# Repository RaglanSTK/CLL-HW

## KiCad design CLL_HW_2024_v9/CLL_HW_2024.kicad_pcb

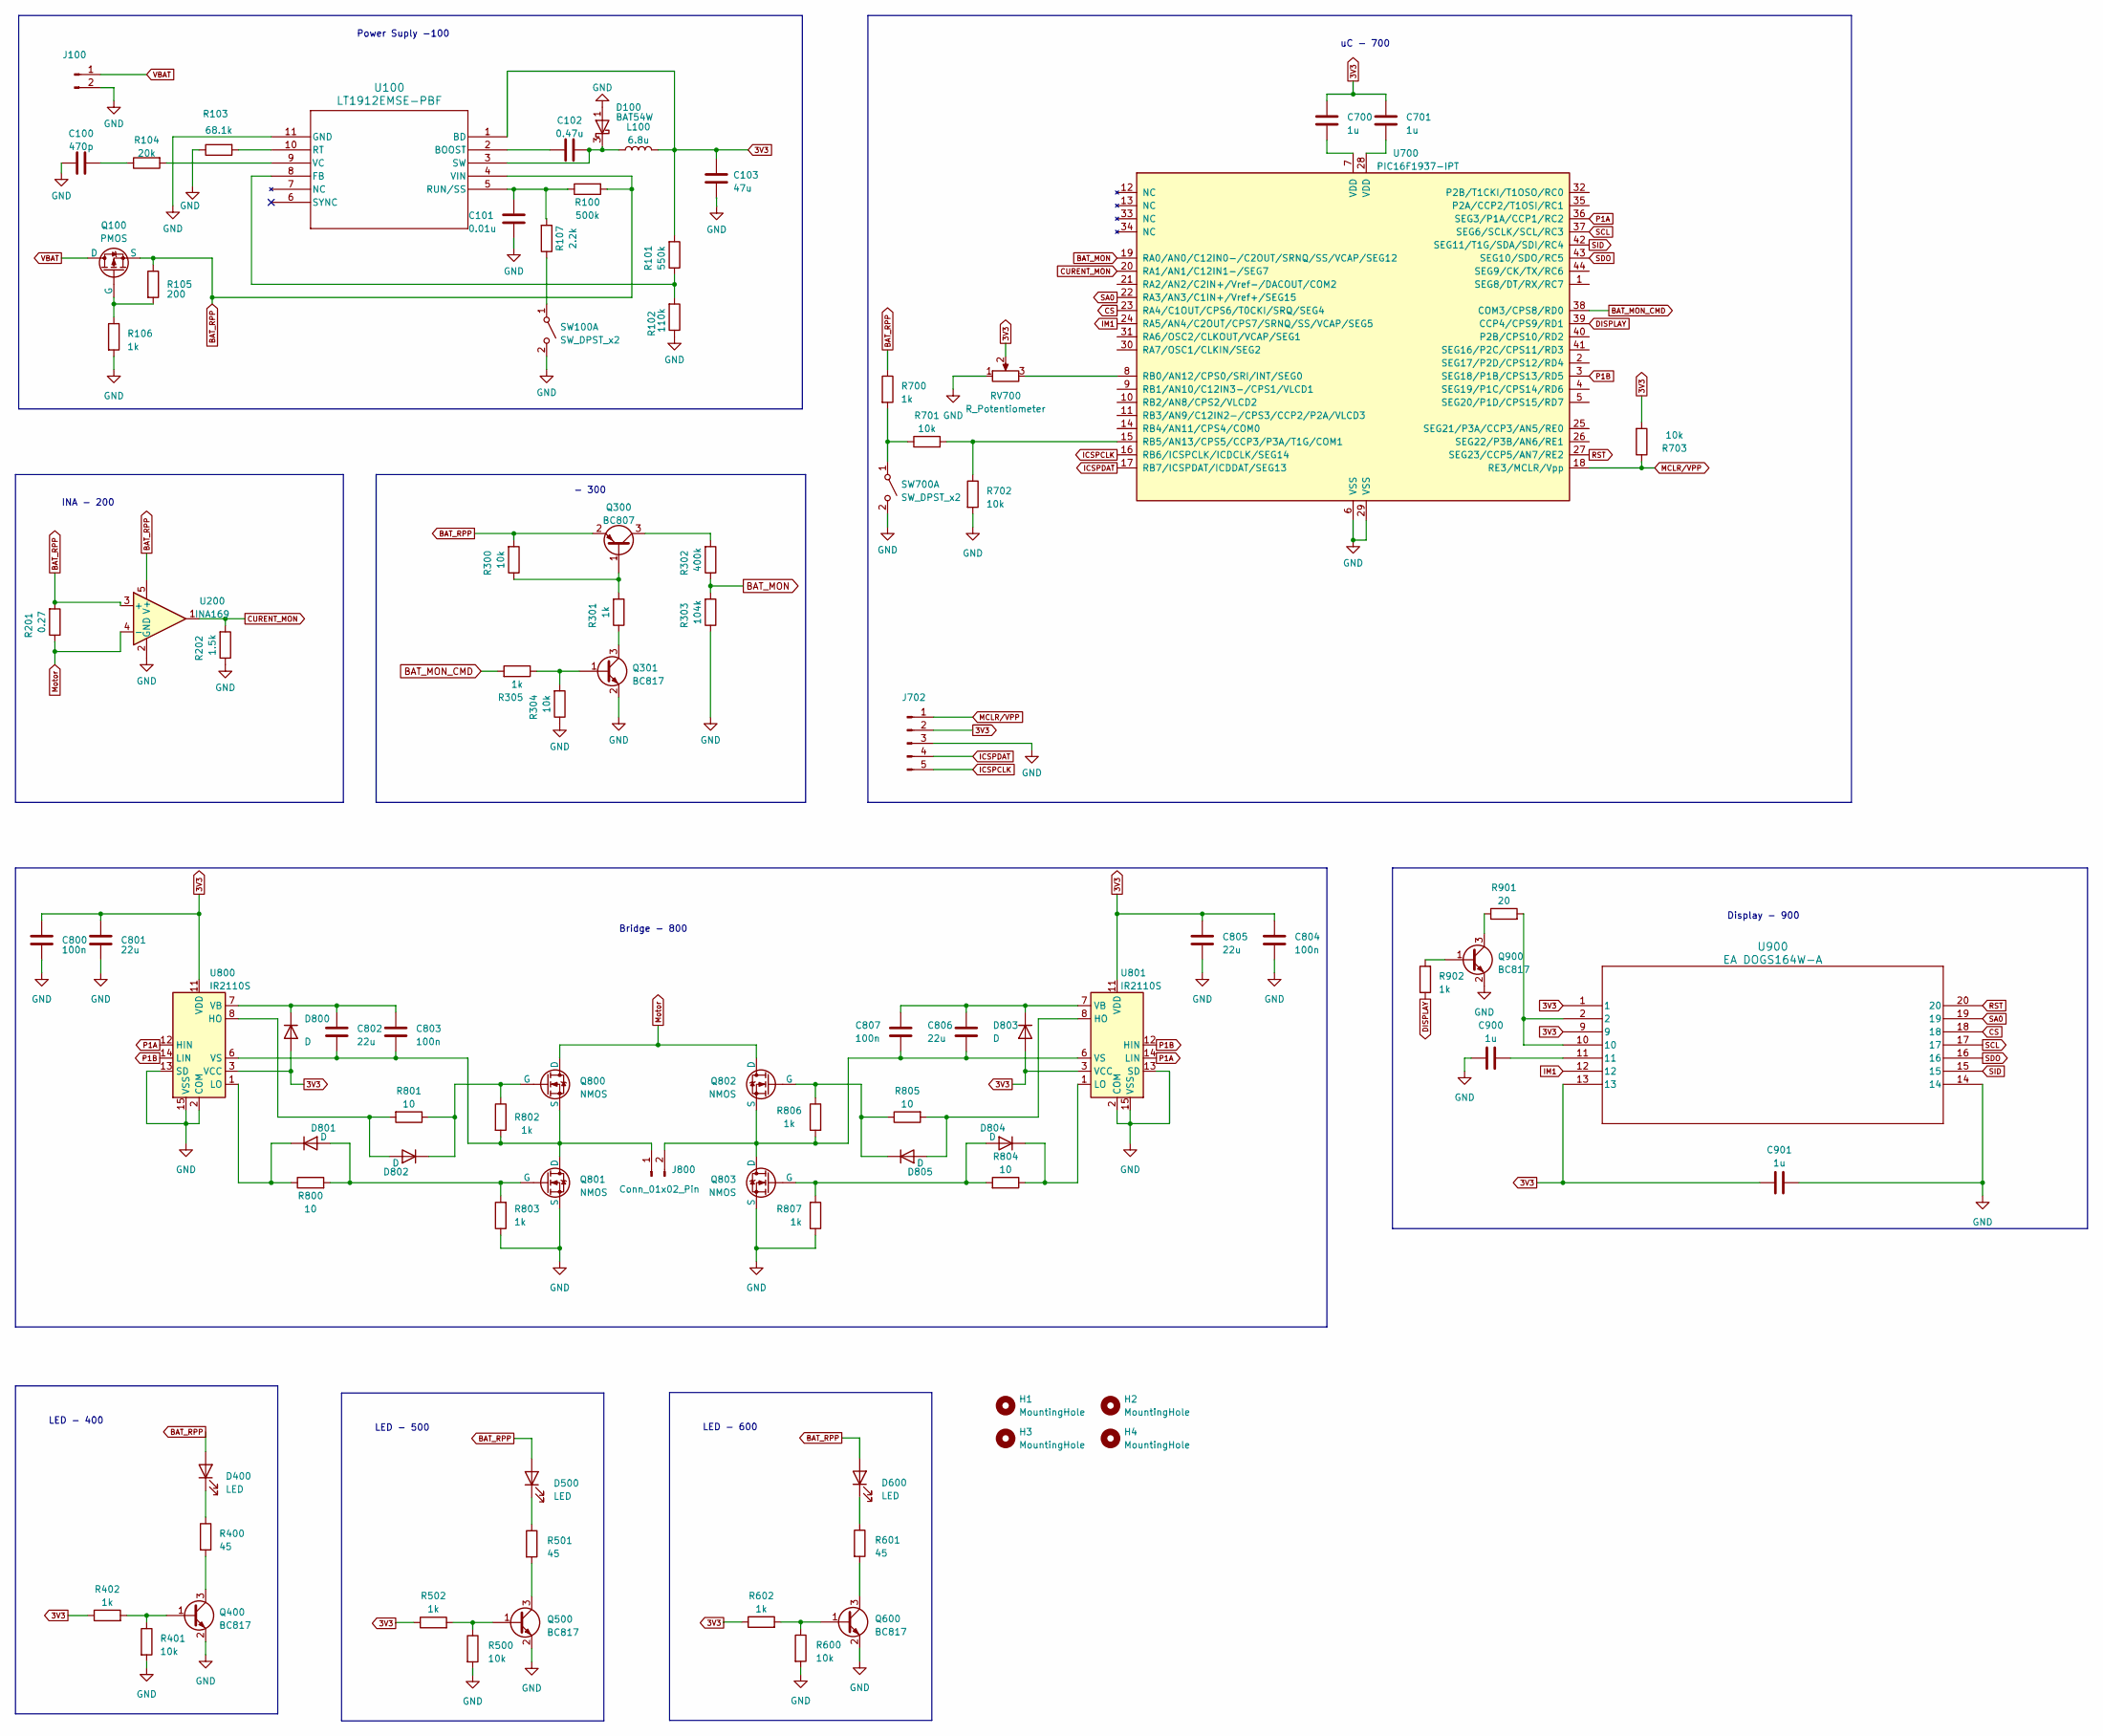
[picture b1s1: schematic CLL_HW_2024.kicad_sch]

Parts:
C100: 470p; C_0805_2012Metric
C101: 0.01u; C_0805_2012Metric
C102: 0.47u; C_0805_2012Metric
C103: 47u; C_0805_2012Metric
C700, C701, C900, C901: 1u; C_0805_2012Metric
C800, C803, C804, C807: 100n; C_0805_2012Metric
C801, C802, C805, C806: 22u; C_0805_2012Metric
D100: BAT54W; SOT-323_SC-70
D400, D500, D600: LED; LED_0805_2012Metric
D800, D801, D802, D803, D804, D805: D; D_SOD-323
H1, H2, H3, H4: MountingHole; MountingHole_2.5mm
J100, J800: Conn_01x02_Pin; TerminalBlock_bornier-2_P5.08mm
J702: Conn_01x05_Pin; PinHeader_1x05_P2.54mm_Vertical
L100: 6.8u; L_0805_2012Metric
Q100: PMOS; SOT-23
Q300: BC807; SOT-323_SC-70
Q301, Q400, Q500, Q600, Q900: BC817; SOT-323_SC-70
Q800, Q801, Q802, Q803: NMOS; SOT-23
R100: 500k; R_0805_2012Metric
R101: 550k; R_0805_2012Metric
R102: 110k; R_0805_2012Metric
R103: 68.1k; R_0805_2012Metric
R104: 20k; R_0805_2012Metric
R105: 200; R_0805_2012Metric
R106, R301, R305, R402, R502, R602, R700, R802, R803, R806, R807, R902: 1k; R_0805_2012Metric
R107: 2.2k; R_0805_2012Metric
R201: 0.27; R_0805_2012Metric
R202: 1.5k; R_0805_2012Metric
R300, R304, R401, R500, R600, R701, R702, R703: 10k; R_0805_2012Metric
R302: 400k; R_0805_2012Metric
R303: 104k; R_0805_2012Metric
R400, R501, R601: 45; R_0805_2012Metric
R800, R801, R804, R805: 10; R_0805_2012Metric
R901: 20; R_0805_2012Metric
RV700: R_Potentiometer; Potentiometer_ACP_CA6-H2,5_Horizontal
SW100, SW700: SW_DPST_x2; SW2_GF-123-0054_CWI
U100: LT1912EMSE-PBF; MSOP-10-1EP_3x3mm_P0.5mm_EP1.68x1.88mm_ThermalVias
U200: INA169; SOT-23-5
U700: PIC16F1937-IPT; TQFP-44_10x10mm_P0.8mm
U800, U801: IR2110S; SOIC-16W_7.5x10.3mm_P1.27mm
U900: EA DOGS164W-A; EA_DOGS104X-A

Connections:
3V3: C103.1, C700.1, C701.1, C800.1, C801.1, C804.1, C805.1, C901.1, D800.2 (A), D803.2 (A), J702.2, L100.2, R101.2, R402.1, R502.1, R602.1, R703.2, RV700.2, U100.1 (BD), U800.3 (VCC), U800.11 (VDD), U801.3 (VCC), U801.11 (VDD), U900.1, U900.9, U900.13
BAT_MON: R302.1, R303.2, U700.19 (RA0/AN0/C12IN0-/C2OUT/SRNQ/SS/VCAP/SEG12)
BAT_MON_CMD: R305.2, U700.38 (COM3/CPS8/RD0)
BAT_RPP: D400.2 (A), D500.2 (A), D600.2 (A), Q100.3 (S), Q300.2 (E), R100.2, R105.1, R201.2, R300.2, R700.1, U100.4 (VIN), U200.3 (+), U200.5 (V+)
CS: U700.23 (RA4/C1OUT/CPS6/T0CKI/SRQ/SEG4), U900.18
CURENT_MON: R202.2, U200.1, U700.20 (RA1/AN1/C12IN1-/SEG7)
DISPLAY: R902.1, U700.39 (CCP4/CPS9/RD1)
GND: C100.2, C101.2, C103.2, C800.2, C801.2, C804.2, C805.2, C900.1, C901.2, D100.1 (A), J100.2, J702.3, Q301.2 (E), Q400.2 (E), Q500.2 (E), Q600.2 (E), Q801.3 (S), Q803.3 (S), Q900.2 (E), R102.1, R103.1, R106.2, R202.1, R303.1, R304.1, R401.2, R500.2, R600.2, R702.2, R803.1, R807.1, RV700.1, SW100.2 (B), SW700.2 (B), U100.11 (GND), U200.2 (GND), U700.6 (VSS), U700.29 (VSS), U800.2 (COM), U800.13 (SD), U800.15 (VSS), U801.2 (COM), U801.13 (SD), U801.15 (VSS), U900.14
ICSPCLK: J702.5, U700.16 (RB6/ICSPCLK/ICDCLK/SEG14)
ICSPDAT: J702.4, U700.17 (RB7/ICSPDAT/ICDDAT/SEG13)
IM1: U700.24 (RA5/AN4/C2OUT/CPS7/SRNQ/SS/VCAP/SEG5), U900.12
MCLR/VPP: J702.1, R703.1, U700.18 (RE3/MCLR/Vpp)
Motor: Q800.1 (D), Q802.1 (D), R201.1, U200.4 (-)
unnamed: C100.1, R104.1
unnamed: C700.2, U700.7 (VDD)
unnamed: C701.2, U700.28 (VDD)
unnamed: C900.2, U900.11
unnamed: C102.1, D100.3 (K), L100.1, U100.3 (SW)
unnamed: D400.1 (K), R400.1
unnamed: D500.1 (K), R501.1
unnamed: D600.1 (K), R601.1
unnamed: C802.1, C803.1, D800.1 (K), U800.7 (VB)
unnamed: D801.2 (A), Q801.2 (G), R800.2, R803.2
unnamed: D801.1 (K), R800.1, U800.1 (LO)
unnamed: D802.2 (A), R801.2, U800.8 (HO)
unnamed: D802.1 (K), Q800.2 (G), R801.1, R802.1
unnamed: C806.1, C807.1, D803.1 (K), U801.7 (VB)
unnamed: D804.2 (A), Q803.2 (G), R804.2, R807.2
unnamed: D804.1 (K), R804.1, U801.1 (LO)
unnamed: D805.2 (A), R805.2, U801.8 (HO)
unnamed: D805.1 (K), Q802.2 (G), R805.1, R806.1
unnamed: C802.2, C803.2, J800.1, Q800.3 (S), Q801.1 (D), R802.2, U800.6 (VS)
unnamed: C806.2, C807.2, J800.2, Q802.3 (S), Q803.1 (D), R806.2, U801.6 (VS)
unnamed: Q100.2 (G), R105.2, R106.1
unnamed: Q300.1 (B), R300.1, R301.2
unnamed: Q300.3 (C), R302.2
unnamed: Q301.1 (B), R304.2, R305.1
unnamed: Q301.3 (C), R301.1
unnamed: Q400.1 (B), R401.1, R402.2
unnamed: Q400.3 (C), R400.2
unnamed: Q500.1 (B), R500.1, R502.2
unnamed: Q500.3 (C), R501.2
unnamed: Q600.1 (B), R600.1, R602.2
unnamed: Q600.3 (C), R601.2
unnamed: Q900.1 (B), R902.2
unnamed: Q900.3 (C), R901.1
unnamed: R901.2, U900.2, U900.10
unnamed: R107.1, SW100.1 (A)
unnamed: R700.2, R701.1, SW700.1 (A)
unnamed: C102.2, U100.2 (BOOST)
unnamed: R101.1, R102.2, U100.8 (FB)
unnamed: R103.2, U100.10 (RT)
unnamed: C101.1, R100.1, R107.2, U100.5 (RUN/SS)
unnamed: R104.2, U100.9 (VC)
unnamed: RV700.3, U700.8 (RB0/AN12/CPS0/SRI/INT/SEG0)
unnamed: R701.2, R702.1, U700.15 (RB5/AN13/CPS5/CCP3/P3A/T1G/COM1)
P1A: U700.36 (SEG3/P1A/CCP1/RC2), U800.12 (HIN), U801.14 (LIN)
P1B: U700.3 (SEG18/P1B/CPS13/RD5), U800.14 (LIN), U801.12 (HIN)
RST: U700.27 (SEG23/CCP5/AN7/RE2), U900.20
SA0: U700.22 (RA3/AN3/C1IN+/Vref+/SEG15), U900.19
SCL: U700.37 (SEG6/SCLK/SCL/RC3), U900.17
SDO: U700.43 (SEG10/SDO/RC5), U900.16
SID: U700.42 (SEG11/T1G/SDA/SDI/RC4), U900.15
VBAT: J100.1, Q100.1 (D)

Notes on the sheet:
Bridge - 800
LED - 600
- 300
Power Suply -100
INA - 200
Display - 900
LED - 400
uC - 700
LED - 500

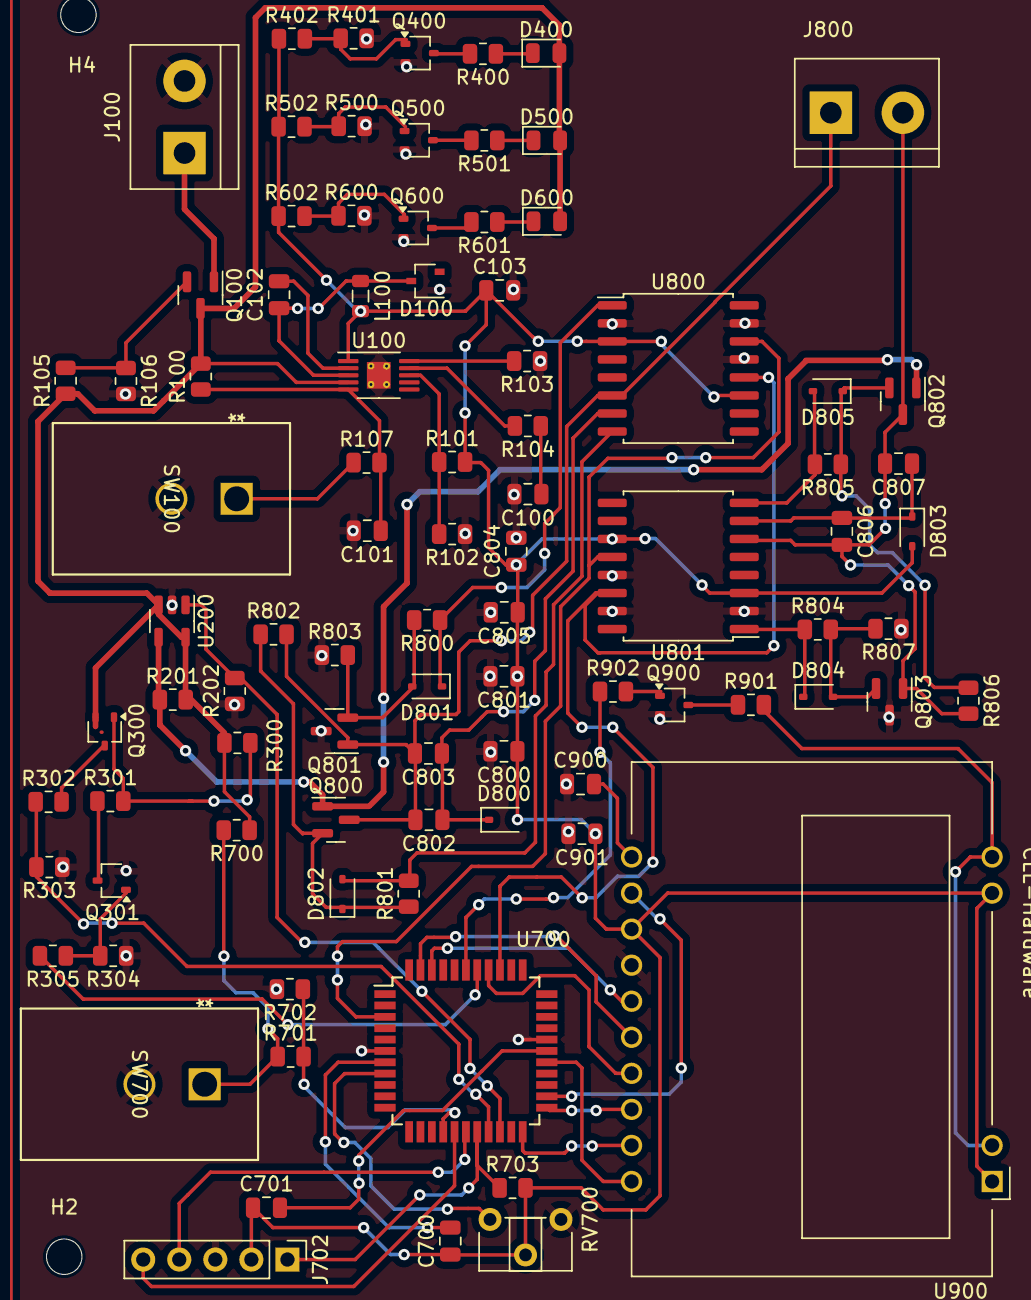
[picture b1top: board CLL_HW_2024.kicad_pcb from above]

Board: 2 copper layers, 93 parts (0 on the bottom side), 64 nets.

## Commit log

2025-03-26 Am adaugat fisier.txt
2025-03-26 Am adaygat un fisier
